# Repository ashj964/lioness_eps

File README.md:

# lioness_eps
Design of LIONESS EPS for CSI CubeSat Mission

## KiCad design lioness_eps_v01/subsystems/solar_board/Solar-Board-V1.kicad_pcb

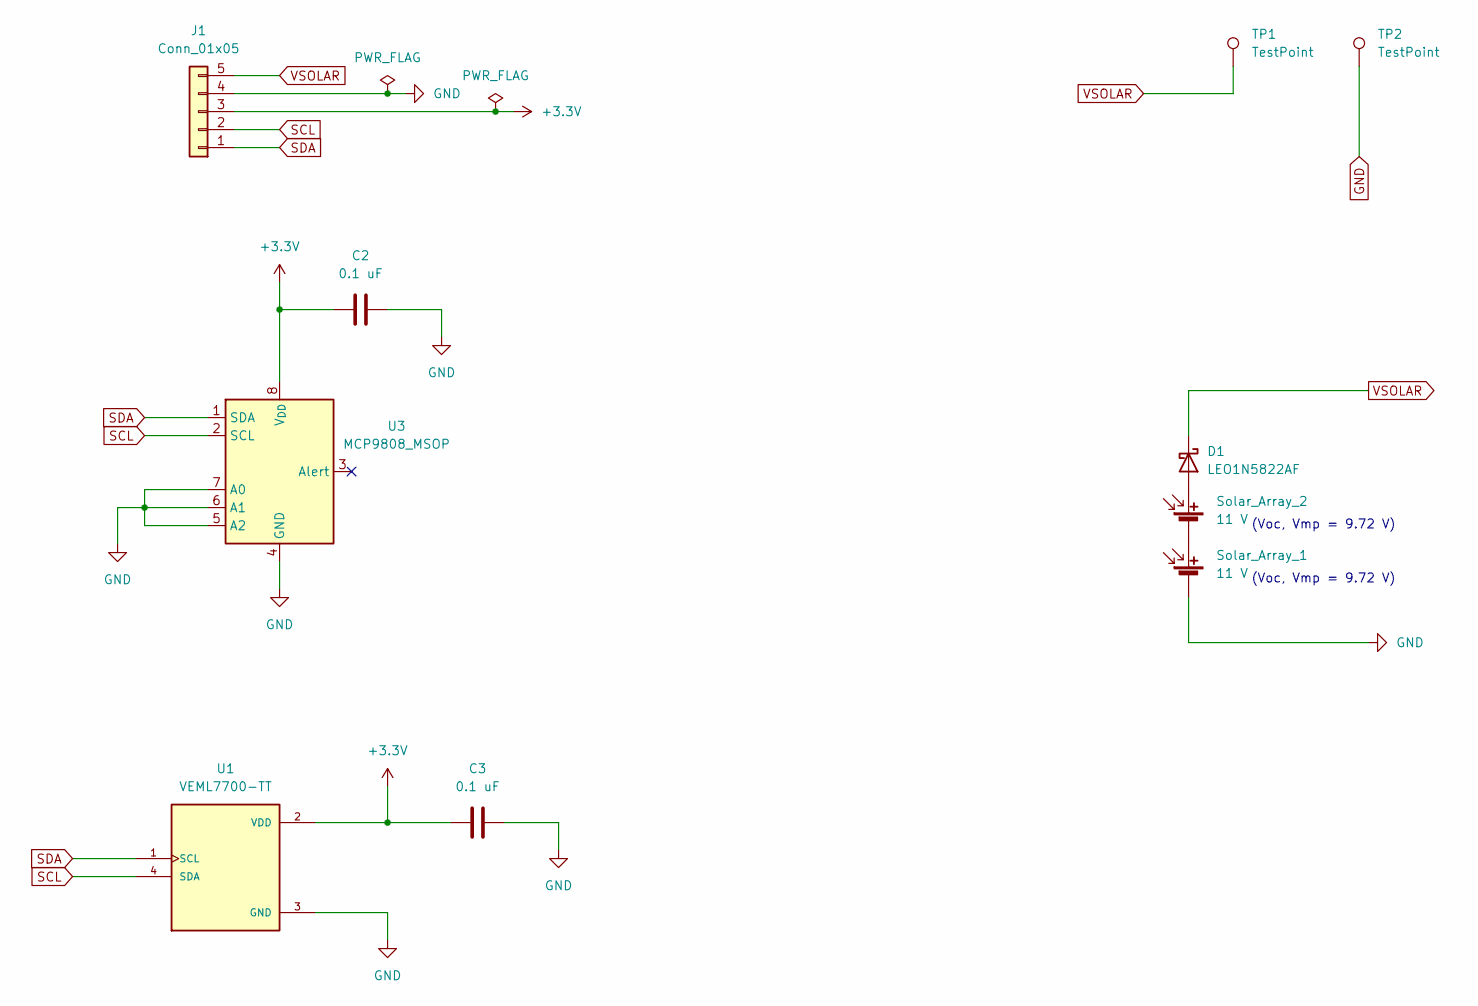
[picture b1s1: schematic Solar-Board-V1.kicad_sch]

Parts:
C2, C3: 0.1 uF; C_0603_1608Metric_Pad1.08x0.95mm_HandSolder
D1: LEO1N5822AF; D_SOD-128
J1: Conn_01x05; Molex_KK-254_AE-6410-05A_1x05_P2.54mm_Vertical
Solar_Array_1, Solar_Array_2: 11 V; Molex_KK-254_AE-6410-02A_1x02_P2.54mm_Vertical
TP1, TP2: TestPoint; TestPoint_Pad_1.0x1.0mm
U1: VEML7700-TT; XDCR_VEML7700-TT; MPN VEML7700-TT
U3: MCP9808_MSOP; MSOP-8_3x3mm_P0.65mm

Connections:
+3.3V: C2.1, C3.1, J1.3, U1.2 (VDD), U3.8 (V_{DD})
GND: C2.2, C3.2, J1.4, Solar_Array_1.2 (-), TP2.1 (1_1), U1.3 (GND), U3.4 (GND), U3.5 (A2), U3.6 (A1), U3.7 (A0)
unnamed: D1.2 (A), Solar_Array_2.1 (+)
unnamed: Solar_Array_1.1 (+), Solar_Array_2.2 (-)
SCL: J1.2, U1.4 (SDA), U3.2 (SCL)
SDA: J1.1, U1.1 (SCL), U3.1 (SDA)
VSOLAR: D1.1 (K), J1.5, TP1.1 (1_1)

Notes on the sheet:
(Voc, Vmp = 9.72 V)

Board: 2 copper layers, 10 parts (0 on the bottom side), 7 nets, no tracks yet.
